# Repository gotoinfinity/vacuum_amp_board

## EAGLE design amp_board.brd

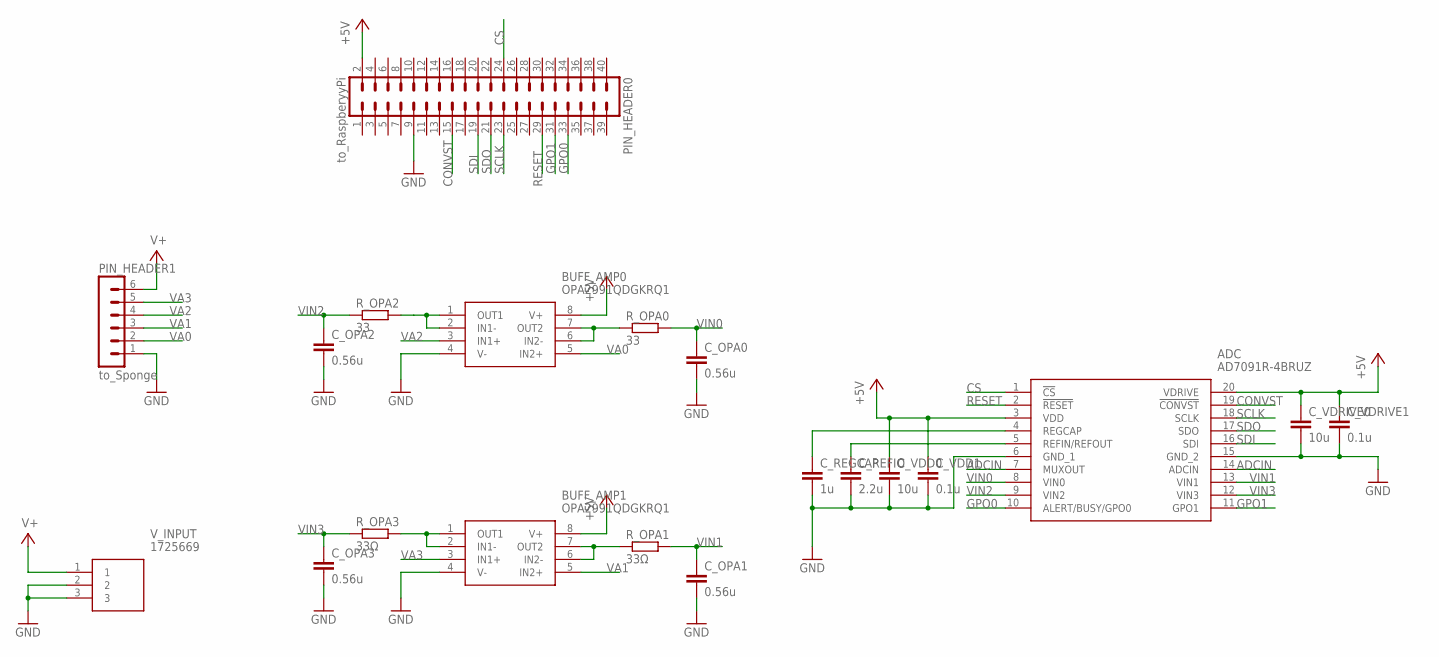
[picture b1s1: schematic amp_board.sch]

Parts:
ADC: AD7091R-4BRUZ; SOP65P640X120-20N
BUFF_AMP0, BUFF_AMP1: OPA2991QDGKRQ1; SOP65P490X110-8N
C_OPA0, C_OPA1, C_OPA2, C_OPA3: 0.56u; C0805
C_REFIO: 2.2u; C0805
C_REGCAP: 1u; C0805
C_VDD0: 10u; C0805
C_VDD1: 0.1u; C0805
C_VDRIVE0: 10u; C0805
C_VDRIVE1: 0.1u; C0805
PIN_HEADER0: to_RaspberyyPi; MA20-2
PIN_HEADER1: to_Sponge; MA06-1
R_OPA0, R_OPA2: 33; R1206
R_OPA1, R_OPA3: 33Ω; R1206
V_INPUT: 1725669

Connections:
+5V: ADC.3 (VDD), ADC.20 (VDRIVE), BUFF_AMP0.8 (V+), BUFF_AMP1.8 (V+), C_VDD0.1, C_VDD1.1, C_VDRIVE0.1, C_VDRIVE1.1, PIN_HEADER0.2
ADCIN: ADC.7 (MUXOUT), ADC.14 (ADCIN)
CONVST: ADC.19 (!CONVST), PIN_HEADER0.15
CS: ADC.1 (!CS), PIN_HEADER0.24
GND: ADC.6 (GND_1), ADC.15 (GND_2), BUFF_AMP0.4 (V-), BUFF_AMP1.4 (V-), C_OPA0.2, C_OPA1.2, C_OPA2.2, C_OPA3.2, C_REFIO.2, C_REGCAP.2, C_VDD0.2, C_VDD1.2, C_VDRIVE0.2, C_VDRIVE1.2, PIN_HEADER0.9, PIN_HEADER1.1, V_INPUT.2, V_INPUT.3
GPO0: ADC.10 (ALERT/BUSY/GPO0), PIN_HEADER0.33
GPO1: ADC.11 (GPO1), PIN_HEADER0.31
unnamed: BUFF_AMP0.1 (OUT1), BUFF_AMP0.2 (IN1-), R_OPA2.2
unnamed: BUFF_AMP1.6 (IN2-), BUFF_AMP1.7 (OUT2), R_OPA1.1
unnamed: BUFF_AMP1.1 (OUT1), BUFF_AMP1.2 (IN1-), R_OPA3.2
unnamed: BUFF_AMP0.6 (IN2-), BUFF_AMP0.7 (OUT2), R_OPA0.1
unnamed: ADC.4 (REGCAP), C_REGCAP.1
unnamed: ADC.5 (REFIN/REFOUT), C_REFIO.1
RESET: ADC.2 (!RESET), PIN_HEADER0.29
SCLK: ADC.18 (SCLK), PIN_HEADER0.23
SDI: ADC.16 (SDI), PIN_HEADER0.19
SDO: ADC.17 (SDO), PIN_HEADER0.21
V+: PIN_HEADER1.6, V_INPUT.1
VA0: BUFF_AMP0.5 (IN2+), PIN_HEADER1.2
VA1: BUFF_AMP1.5 (IN2+), PIN_HEADER1.3
VA2: BUFF_AMP0.3 (IN1+), PIN_HEADER1.4
VA3: BUFF_AMP1.3 (IN1+), PIN_HEADER1.5
VIN0: ADC.8 (VIN0), C_OPA0.1, R_OPA0.2
VIN1: ADC.13 (VIN1), C_OPA1.1, R_OPA1.2
VIN2: ADC.9 (VIN2), C_OPA2.1, R_OPA2.1
VIN3: ADC.12 (VIN3), C_OPA3.1, R_OPA3.1

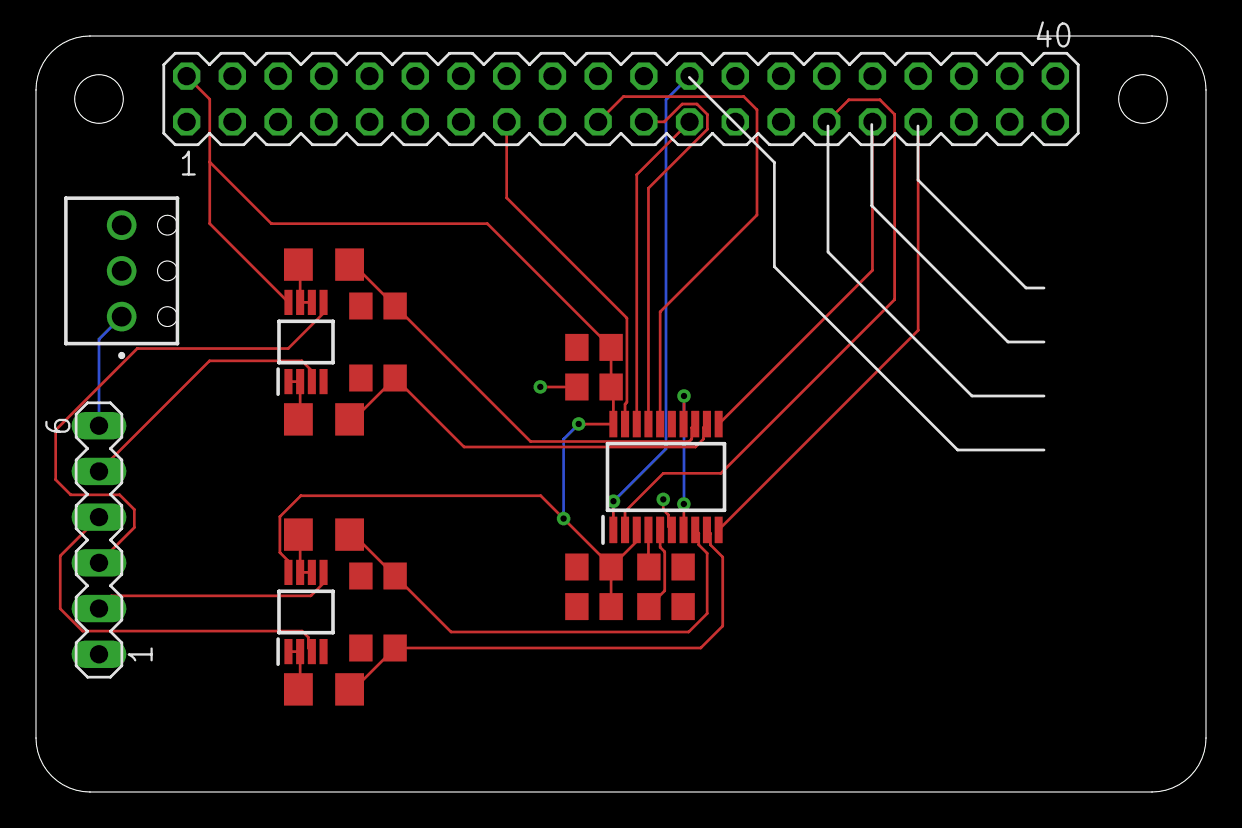
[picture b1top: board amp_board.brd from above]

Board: 2 copper layers, 65.0 x 42.0 mm, 20 parts (0 on the bottom side), 26 nets.

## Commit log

2022-05-13 upload files
